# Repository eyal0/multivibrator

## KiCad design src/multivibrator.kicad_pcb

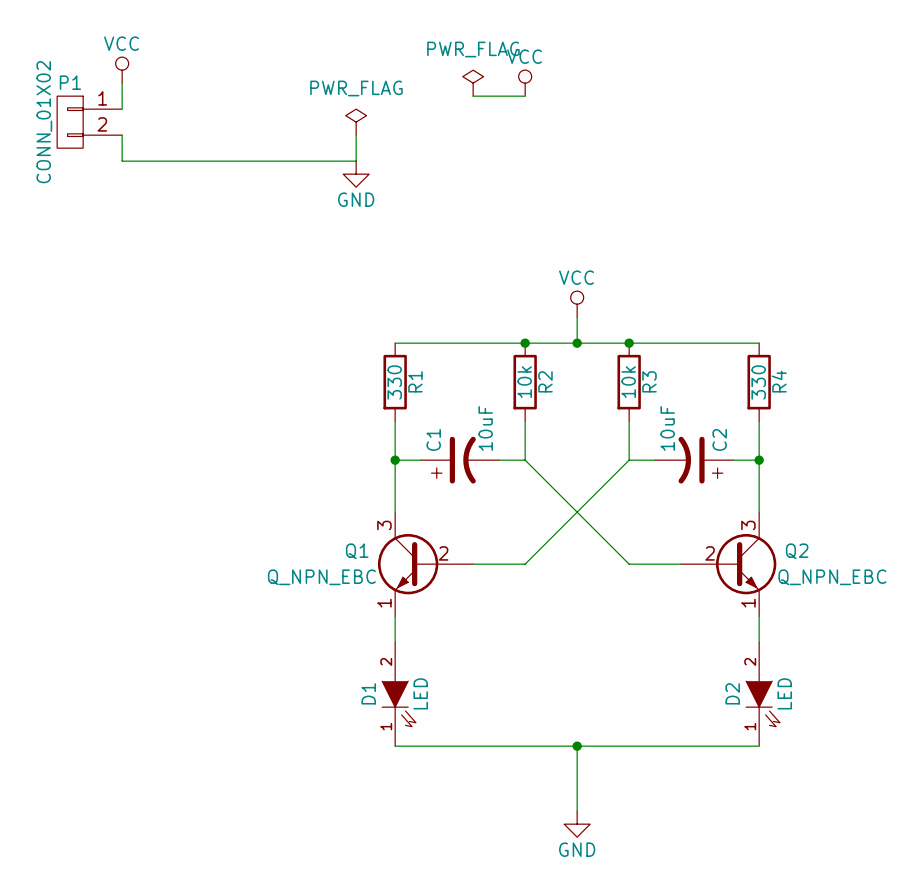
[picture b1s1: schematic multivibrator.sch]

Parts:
C1, C2: 10uF; C_Radial_D5_L6_P2.5
D1, D2: LED; LED-5MM
P1: CONN_01X02; Socket_Strip_Straight_1x02_Pitch2.54mm
Q1, Q2: Q_NPN_EBC; TO-92_Inline_Wide
R1, R4: 330; Resistor_Horizontal_RM7mm
R2, R3: 10k; Resistor_Horizontal_RM7mm

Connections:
GND: D1.1 (K), D2.1 (K), P1.2
unnamed: C1.1, Q1.3 (C), R1.2
unnamed: C1.2, Q2.2 (B), R2.2
unnamed: C2.1, Q2.3 (C), R4.2
unnamed: C2.2, Q1.2 (B), R3.2
unnamed: D1.2 (A), Q1.1 (E)
unnamed: D2.2 (A), Q2.1 (E)
VCC: P1.1, R1.1, R2.1, R3.1, R4.1

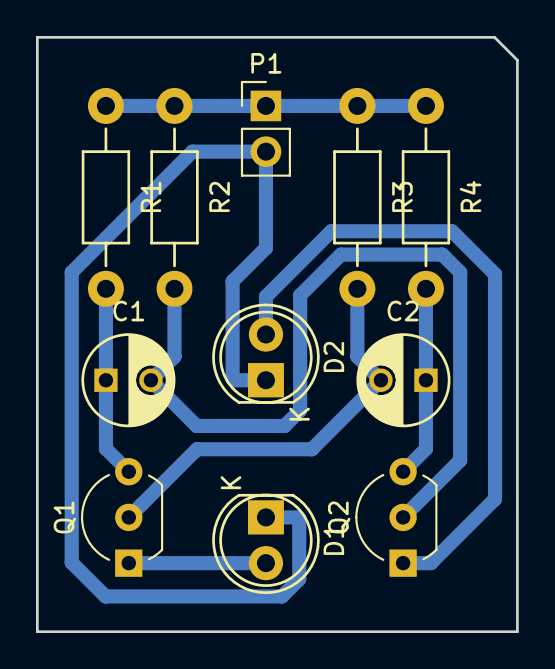
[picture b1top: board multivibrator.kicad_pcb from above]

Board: 2 copper layers, 26.7 x 33.0 mm, 11 parts (0 on the bottom side), 8 nets.

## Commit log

2017-04-30 First PCB
2017-05-09 add even the generated files
2017-05-09 unify_gcode.py and updated millproject
2017-05-09 adjust the depths of the cutting and drilling
2017-05-09 mill a little deeper and make the bridges more narrow
2017-05-10 moved silk around
2017-05-10 switch transsitor footprint
2017-05-10 ebc npn transistors laid out
2017-05-10 regenerate the gerbers
2017-05-10 clean up a tiny track on pcb and regen cnc
2017-05-10 clean up one slope
2017-05-14 replot svg files
2017-05-14 rebuild on desktop the ngc file
2017-05-15 remove unneeded gbr files in root
2017-05-15 some scripts working
2017-05-15 makefile
2017-05-15 remove the intermediate dirs gerber, cnc, svg, etc
2017-05-15 gitignore
2017-05-15 put files in src dir
2017-05-15 add b.mask to plot_board
2017-05-15 add the gerbmerge files
2017-05-15 gerbmerg.cfg outfile destinations and excellondecimals
2017-05-15 don't write the ToolList
2017-05-15 pcb2gcode on the panelized version, it works
2017-05-16 expand g85 in progress
2017-05-16 exapnd_g85 looks okay
2017-05-16 Use expand_g85 in makefile
2017-05-16 use panelized version for drilling and use pcb2gcode from git and not installed
2017-05-18 make svg from panelized
2017-05-18 split ngcs to two files
2017-05-18 makefile to build two ngc files
2017-05-18 cut corner of pcb for alignment
2017-05-18 get rid of the nog85 stuff
2017-05-18 use smaller connector
2017-05-21 update kicad, rotate connector, clean up trace
2017-05-21 use 2.5mm cutter
2017-06-29 made a smaller pcb?
2017-06-29 touch up
2017-06-29 5 copies per PCB
2017-07-02 remove multivibrator-rescue lib
